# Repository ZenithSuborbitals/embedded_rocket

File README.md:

### Software and Electrical Components of a Suborbital Sounding Rocket's Telemetry System

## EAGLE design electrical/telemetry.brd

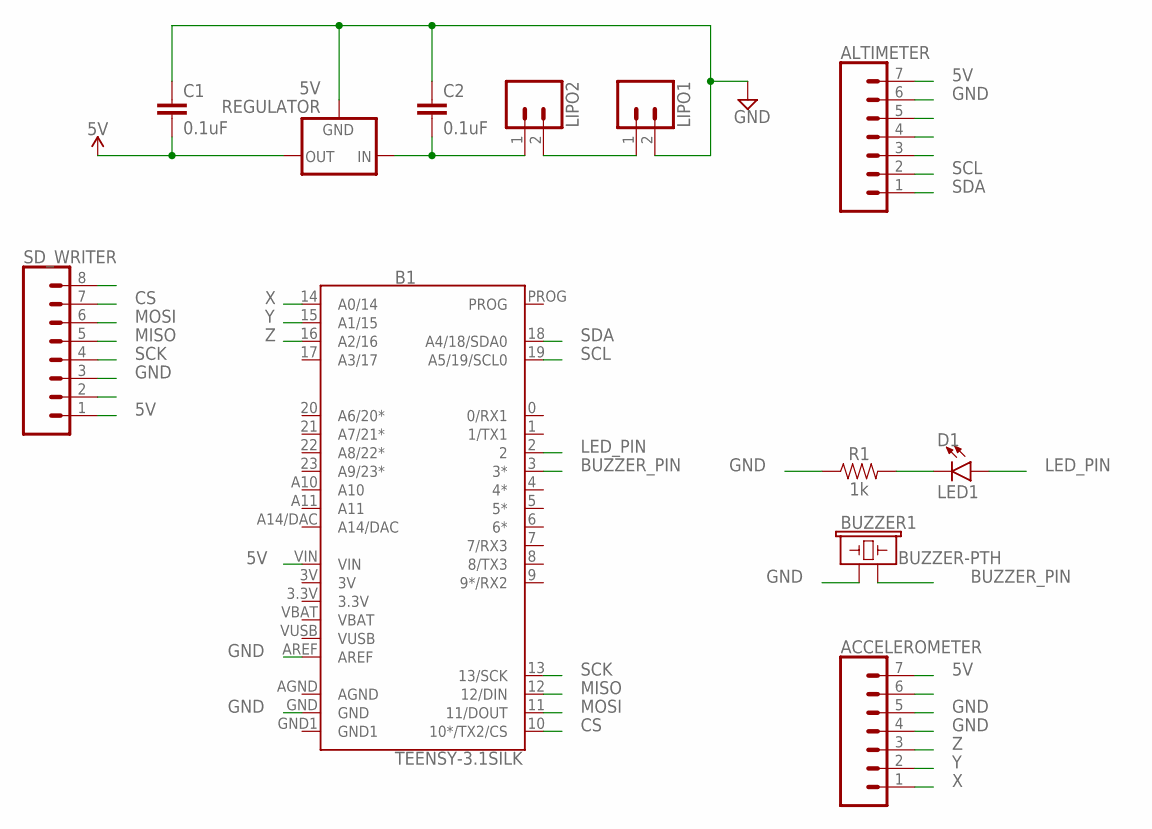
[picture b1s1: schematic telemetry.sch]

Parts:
ACCELEROMETER: CONN_07; 1X07
ALTIMETER: CONN_07; 1X07
B1: TEENSY-3.1SILK; TEENSY-3.1
BUZZER1: BUZZER-PTH; BUZZER-12MM
C1, C2: 0.1uF; CAP-PTH-SMALL-KIT
D1: LED1; LED_5MM
LIPO1, LIPO2: CONN_02; 1X02
R1: 1k; AXIAL-0.3
REGULATOR: 5V; 78XXS
SD_WRITER: CONN_08"; 1X08

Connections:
3.3V: B1.3.3V
3V: B1.3V
5V: ACCELEROMETER.7, ALTIMETER.7, B1.VIN, C1.2, REGULATOR.OUT, SD_WRITER.1
AGND: B1.AGND
BUZZER_PIN: B1.3 (3*), BUZZER1.- (2)
CS: B1.10 (10*/TX2/CS), SD_WRITER.7
GND: ACCELEROMETER.4, ACCELEROMETER.5, ALTIMETER.6, B1.AREF, B1.GND, BUZZER1.+ (1), C1.1, C2.1, LIPO1.2, R1.P$1 (1), REGULATOR.GND, SD_WRITER.3
GND1: B1.GND1
LED_PIN: B1.2, D1.A
MISO: B1.12 (12/DIN), SD_WRITER.5
MOSI: B1.11 (11/DOUT), SD_WRITER.6
unnamed: LIPO1.1, LIPO2.2
unnamed: C2.2, LIPO2.1, REGULATOR.IN
unnamed: D1.K (C), R1.P$2 (2)
SCK: B1.13 (13/SCK), SD_WRITER.4
SCL: ALTIMETER.2, B1.19 (A5/19/SCL0)
SDA: ALTIMETER.1, B1.18 (A4/18/SDA0)
VBAT: B1.VBAT
VUSB: B1.VUSB
X: ACCELEROMETER.1, B1.14 (A0/14)
Y: ACCELEROMETER.2, B1.15 (A1/15)
Z: ACCELEROMETER.3, B1.16 (A2/16)

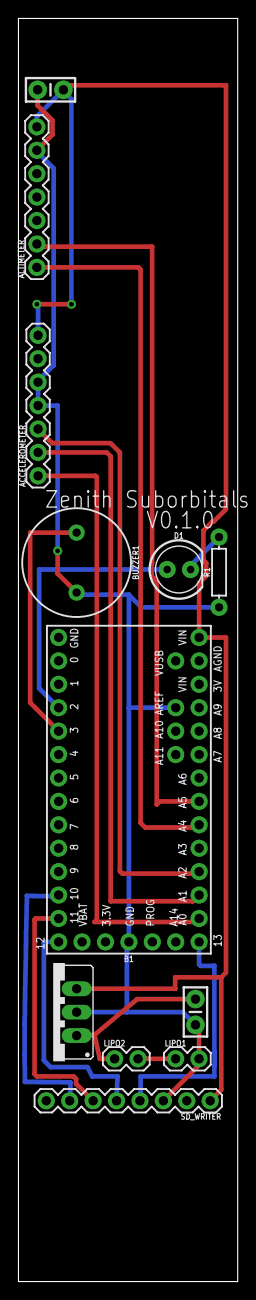
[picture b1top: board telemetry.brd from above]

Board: 2 copper layers, 23.8 x 137.0 mm, 12 parts (0 on the bottom side), 16 nets.

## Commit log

2017-10-13 updated pins
2017-10-15 updated structure

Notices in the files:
parts and their libraries:
SparkFun-Connectors: Licensing: Creative Commons ShareAlike 4.0 International - https://creativecommons.org/licenses/by-sa/4.0
